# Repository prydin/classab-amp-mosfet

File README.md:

# 50W Class AB MOSFET Amplififier

## Disclaimer
This amplifier has been built and tested and, at least subjectively speaking, sounds great. However, I'm not a professional designer
and this is my first "serious" attempt at amplifier design. I invite you to build this amplifier if you like, but don't expect it to
perform like a professionally designed high-end amplifier. That said, I think it sounds pretty darn good. 

## Background
This is an updated version of the bipolar Class AB amplifier I designed a while ago that can be found here: https://github.com/prydin/classab-amp
I tried to correct some of the mistakes (mostly in the PCB design) and I also wanted to try use MOSFETs for the output stage. I settled on the 
tried and tested IRFP240/9240 combination. Although not marketed as audio transistors, these devices have found their way into countless amplifier 
designs, perhaps most notably some of Nelson Pass' First Watt creations. I really like the way they're performing. They seem to run a lot cooler
at the same quiescent current compared to their BJT counterparts. I'm also seeing less distortion and mostly concentrated on the second harmonic.

## Repository structure
* `kicad` - Schematic and PCB layout in KiCAD format
*  `spice` - LTSpice simulations

## Overall design
The design is a simple single differential stage amplifier with a single ended, two transistor emitter coupled VAS driving two complementary
MOSFETs on the output.

### Input stage
After the customary DC-blocking capacitor and RF filter, the signal is fed into a long tailed pair differential amplifier that's enhanced to 
an active current sink and current mirror loads. The active sink and load helps improve both distortion and frequency response. The bias 
current of the LTP is set to approximately 1.5mA. The LTP and its current mirrors are placed closely togethe for maximum heat
condudctivity between the transistors. If so desired, they can be put into physical contact using a brace or a zip tied.
The feedback is fed through a 22k/1k voltage divider, yielding about 23x (27dB) gain. This is a conservative estimate and may have to 
be adjusted when testing the physical build. The active current sink and load seem to offer a robustpower supply rejection. 

### Voltage amplification/drive stage
I went for a very simple single-sided design here. I've gotten many suggestions that I should try a dual differential design instead, but 
the current design seems good enough, so I stuck with it. The VAS has a 220pF compensation capacitor which appears to be enough to provide 
ample phase margin. 

### Output stage biasing
The output stage is biased using a servo transistor driven by a constant current sink. The BD139 for the servo as chosen just because it's
easy to mount on a heat sink together with the power components for good heat conductivity between components. A much less powerful 
transistor works too, but would have been harder to attach to the heat sink.

### Output stage
The output stage consists of a complementary pair made up of IRFP240/9240 MOSFETs with a 330ohm gate resistor. 
Before the signal reaches the speaker, it is passed througha snubber and an inductor to further improve stability.

### Short circuit projection 
Rather than the "base current thief" arrangement in the BJT version, I'm solely relying on a pair of zener diodes to keep the 
gate voltage about 5V above or below the source voltage. This limits the power to about 50W and results in fairly soft clipping. 

### Output coil
The output coil is realized simply by winding 10-12 turns of 16 AWG wire around R21. See the photo below!

### Power improvements
Altough this hasn't been tested or thorouhgly analyzed, it should be possible to increase the rail voltages to +-40V, which yields about
160W according to simultions. For this to work, the gain needs to be made higher by increasing the value of the feedback resistor. The voltage 
limiting zener diodes on the gates also have to be adjusted.

### Power supply
The amplifier is intended to be powered by an unregulated linear power supply like the one supplied in this repository. Each amplifier board
is fitted with 4700uF on each rail, per channel and the rectifier board has an additional 9400uF on each rail. In simulations, measurements 
and listening tests, this seems sufficient. 

The amplifier has been tested with rail voltages ranging from +-24V to +-37V with good results. Obviously, higher output power requires more voltage. 
The recommended supply voltage range is +-24V to +-40V. 

In my build, I'm using a 2x25V toroidial transformer. Where I live, this ended up giving me 2x39V rectified voltage, which is a bit overkill for
50W, but some extra headroom is never a bad thing.

### PCB Design
I am *NOT* an expert at PCB design. In fact, I'm very much a novice and not very good at it, so the PCB layout is probably somewhat naive. 
In this design, I tried to create a star arrangement for the power ground. The power ground is loosely connected to the signal ground through 
a 100ohm resistor and to the chassis through a 220ohm resistor and a 10nF capacitor. This is slightly different from the prototype that I 
originally built, so you may have to tweak this if you experience hum. The prototype I'm currently using in my livingroom has no audible hum.

# Build and bring-up

## Mechanincal design
Mechnical design is not my forte, so you're probably best off to come up with your own design here. I went with a 11' x 10' metal case
from Nobsound. This proved to be rather small with the beefy 250VA transformer I picked, so wire routing turned out to be a challenge. 
I wouldn't be offended if you called it a rat's nest. I used a pair of inexpensive finned aluminum heatsinks from Amazon and they seem to 
work very well. During casual listening at a moderate volume, they stay more or less room temperature. 

## Thermal coupling
It is *extremely* important that Q7, Q9 and Q10 are thermally coupled, i.e. mounted on the same heat sink. Failure to do this 
may result in thermal runaway and catastrophic damage to the output stage! 

You may also want to thermally couple the two transistor pairs in the input stage (R1 and R2, and R3 and R4 respectively). I just 
wrapped a piece if ziptie around them to make them touch. 

## Bring-up
This is the procedure I followed when bringing it up the first time. It saved me on the first bring-up since I had accidentally mixed up 
the transistors in the LTP which put DC on the speaker output.

1. Disconnect the speakers.
2. Turn the bias trimmer to its lowest setting (highest resistance)
3. Connect a current limited power supply with -12V, 0V and +12V to the power inputs. Limit the current to 200mA. The amplifier should draw less than 100mA.
4. Measure the DC voltage across the speaker terminals. It should be less than 50mV. 
5. Connect an oscilloscope to the output. There should be no oscillations.
6. Slowly bring the voltage to +/-24V. The current draw should still be well below 100mA.
7. Connect a 8Ω resistive dummy load to the output. The current draw should not increase significantly.
8. Connect a signal generator to the input and send in a 10mV p/p 1kHz sine singal. You should see approximately 200mV p/p on the speaker output.
9. Increase the current limit to 500mA and try the same with a 100mV p/p and 200mV p/p signal.
10. Increase the current limit to 1A and try a 300mV p/p input.
11. Connect the speakers and feed a music signal. It it may not sound perfect, since lab supplies aren't designed to power amplifiers, but there should be no severe distortion. 
13. Hook up the amplifier to the power supply that will be used for the final build. I put 3A fuses in series with each rail.
14. Measure DC voltage on the speaker outputs. The DC voltage should not exceed 50mV. 
15. Measure the voltage between the emitters on the output transistors (Q9 and Q10). Adjust the bias trim until the voltage reaches 20mV. This corresponds to a bias current of 30mA.
    Verify that the heat sinks are no warmer than luke warm. You may go higher or lower depending on your preferences. Just watch the temperatures!
17. Bring up the amplifer and test it using a dummy load and signal generator as described above.
18. If all has gone well up until this point, connect your speakers and crank up your favorite tune. ENJOY!

# Schematic

## Stats

All simulations are done with an 8 ohm resistive dummy load, 1V input at 1kHz.

### THD (simulated)
At a fairly moderate quiescent current of 45mA, I get a THD20k of 0.003% at 30% power. A THD below 0.1% is considered to be inaudible, so these numbers
are fine by me. I know there are audiophiles who insist on THD numbers <0.0001%, but I'm not one of them. Inaudible is just fine by me. The THD at full
power (50W) is about 0.1%.

I unfortunately don't have the equipment to accurately measure THD in the lab, but it looks to be considerably below 0.1% (probably below 0.01%).

```
Fourier components of V(out)
DC component:-0.00638947

Harmonic	Frequency	 Fourier 	Normalized	 Phase  	Normalized
 Number 	  [Hz]   	Component	 Component	[degree]	Phase [deg]
    1   	 1.000e+3	 1.137e+1	 1.000e+0	   90.67°	    0.00°
    2   	 2.000e+3	 2.313e-4	 2.034e-5	  -82.88°	 -173.56°
    3   	 3.000e+3	 1.539e-4	 1.354e-5	  176.54°	   85.87°
    4   	 4.000e+3	 1.334e-4	 1.174e-5	  -87.58°	 -178.26°
    5   	 5.000e+3	 1.239e-5	 1.090e-6	 -166.62°	 -257.29°
    6   	 6.000e+3	 9.620e-5	 8.462e-6	  -84.00°	 -174.67°
    7   	 7.000e+3	 5.301e-5	 4.663e-6	    6.49°	  -84.19°
    8   	 8.000e+3	 6.785e-5	 5.968e-6	  -81.59°	 -172.26°
    9   	 9.000e+3	 6.897e-5	 6.067e-6	    8.04°	  -82.64°
   10   	 1.000e+4	 4.481e-5	 3.942e-6	  -78.43°	 -169.11°
   11   	 1.100e+4	 6.376e-5	 5.608e-6	    9.49°	  -81.19°
   12   	 1.200e+4	 2.633e-5	 2.316e-6	  -73.92°	 -164.59°
   13   	 1.300e+4	 5.062e-5	 4.453e-6	   10.82°	  -79.85°
   14   	 1.400e+4	 1.270e-5	 1.117e-6	  -65.17°	 -155.85°
   15   	 1.500e+4	 3.641e-5	 3.203e-6	   11.89°	  -78.79°
   16   	 1.600e+4	 4.245e-6	 3.734e-7	  -33.69°	 -124.37°
   17   	 1.700e+4	 2.420e-5	 2.129e-6	   12.70°	  -77.97°
   18   	 1.800e+4	 3.632e-6	 3.195e-7	   53.21°	  -37.47°
   19   	 1.900e+4	 1.499e-5	 1.318e-6	   12.97°	  -77.70°
   20   	 2.000e+4	 5.428e-6	 4.775e-7	   75.45°	  -15.22°
Harmonic Distortion: 0.003150%
```

### AC Analysis (measured)
The amplifier has a 3dB bandwidth of about 250kHz, which is respectable, while not in the hardcore audiophile range, but it keeps any poles far away from the audible 
range to make both the amplitude and phase response vritually flat where it matters. I am of the opinion that nothing >20kHz has any impact on
the listening experience.

# Bill of materials

All capacitor voltages are 50V and all resistor power ratings are 1/4W unless otherwise indicated. 
1% tolerance resistors are recommended.

## Amplifier Board (each channel)

| Reference | Value | Footprint | Qty | Vendor| Part No | 
| --------- | ----- | --------- | ----| ----- | ------- |
| C1 | 33uF, non-polarized | Radial_D4.0mm_P2.00mm | 1 | Generic | | 
| C2,C5 | 100pF | Rect_L7.2mm_W3.0mm_P5.00mm | 2 | Generic | |
| C4 | 220uF | Radial_D8.0mm_P5.00mm | 1 | Mouser | 871-B32529C1104J |
| C6 | 10uF | CRadial_D4.0mm_P2.00mm | 1 | Mouser | 710-860240672002 |
| C7 | 10nF | Rect_L7.2mm_W3.0mm_P5.00mm | 1 | Generic | |
| C13,C14 | 4700uF | CP_Radial_D18.0mm_P7.50mm | 2 | Mouser | 232-50PK4700MEFC18X4 | 
| D4,D5 | 1N4148 | DO-35_SOD27_P7.62mm | 2 | Mouser | 512-1N4148 |
| D6,D11 | 1N5919 |DO-41_SOD81_P10.16mm | 2 | Mouser | 863-1N5919BRLG |
| D7,D8,D9,D10 | 1N4004 | DO-41_SOD81_P10.16mm | 4 | Mouser | 637-1N4004 | 
| J1 | Terminal Block | TerminalBlock_Phoenix_MKDS-1,5-2_1x02_P5.00mm | 1 | Generic |
| J2,J4,J5 | Spade connector, male | Pitch 5.08mm, hole 1.4mm | 3 | Generic | |
| J3 | Terminal Block | TerminalBlock_4Ucon_1x02_P3.50mm_Horizontal | 1 | Generic | |
| Q1,Q2,Q11,Q12,Q15 | 2N5551 | TO-92_Wide | 5 | Mouser | 583-2N5551-T |
| Q3,Q4,Q16 | 2N5401 | TO-92_Wide | 3 | Mouser | 583-2N5401-F |
| Q6 | BD140 | TO-126-3_Vertical | 1 | Mouser | 511-BD140-16 |
| Q7,Q8 | BD139 | TO-126-3_Vertical | 2 | Mouser | 511-BD139-16 |
| Q9 | IRFP240 | TO-247-3_Vertical | 1 | Mouser | 844-IRFP240PBF |
| Q10 | IRFP9240 | TO-247-3_Vertical | 1 | Mouser | 844-IRFP9240PBF |
| R1 | 150 | L6.3mm_D2.5mm_P2.54mm | 1 | Mouser | 660-MF1/4LCT52R151J |
| R2,R9 | 22k | L6.3mm_D2.5mm_P2.54mm | 2 | Mouser | MFR-25FTE52-22K | 
| R3,R4,R5 | 470 | L3.6mm_D1.6mm_P7.62mm | 3 | Mouser | 660-MF1/4DCT52R4700F |
| R6,R11 | 4.7k | L3.6mm_D1.6mm_P7.62mm | 2 | Mouser | 660-MF1/4LCT52R472G |
| R7,R19 | 1k | L3.6mm_D1.6mm_P7.62mm | 2 | Mouser | 279-LR0204F1K0 |
| R8,R12,R18 | 330 | L3.6mm_D1.6mm_P7.62mm | 3 | Mouser | 660-MF1/4LCT52R331J |
| R10,R14,R22 | 100 | L3.6mm_D1.6mm_P7.62mm | 3 | Generic | |
| R13 | 10k | L3.6mm_D1.6mm_P7.62mm | 1 | Generic | |
| R15 | 220 / 3W | L11.9mm_D4.5mm_P15.24mm | 1 | Mouser | 	603-FMP300JTF73-220R |
| R16,R17 | 0.33 / 3W | L11.9mm_D4.5mm_P15.24mm | 2 | Mouser | 71-PAC300003307FAC00 |
| R20,R21 | 10 / 3W | L11.9mm_D4.5mm_P15.24mm | 2 | Mouser | EP3WSS10RJ | 
| RV1,RV2 | 300 | TRIM_T93YA103KT20 | 2 | Amazon | https://www.amazon.com/BOJACK-Multiturn-Trimmer-Potentiometer-Assortment/dp/B07WDCVGJV |

## Rectifier board

| Reference | Value | Footprint | Qty | Vendor| Part No | 
| --------- | ----- | --------- | ----| ----- | ------- |
| C1,C2,C5,C6 | 4700uF | CP_Radial_D18.0mm_P7.50mm | 4 | Mouser | 232-50PK4700MEFC18X4 | 
| C3,C4,C7 | 100n | Rect_L7.2mm_W5.5mm_P5.00mm | 3 | Generic | |
| D1,D2,D3,D4 | GI754 | D_P600_R-6_P12.70mm | 4 | Mouser | 625-GI754-E3/73 |
| J1, J2, J3, J4, J5, J6 | Spade connector, male | Pitch 5.08mm, hole 1.4mm | 6 | Generic | |

## Transformer
| Reference | Value | Footprint | Qty | Vendor| Part No | 
| --------- | ----- | --------- | ----| ----- | ------- |
| TR1 | 25V / 250VA | N/A | 1 | Avel Lindberg | Y236652 |

## Case and hardware 
* Case: https://www.aliexpress.us/item/3256807449187155.html?src=google&gatewayAdapt=glo2usa
* Heatsink: https://www.amazon.com/Awxlumv-Aluminum-60x150x25mm-2-36x5-91x0-98-Amplifier/dp/B07VDHQDQT

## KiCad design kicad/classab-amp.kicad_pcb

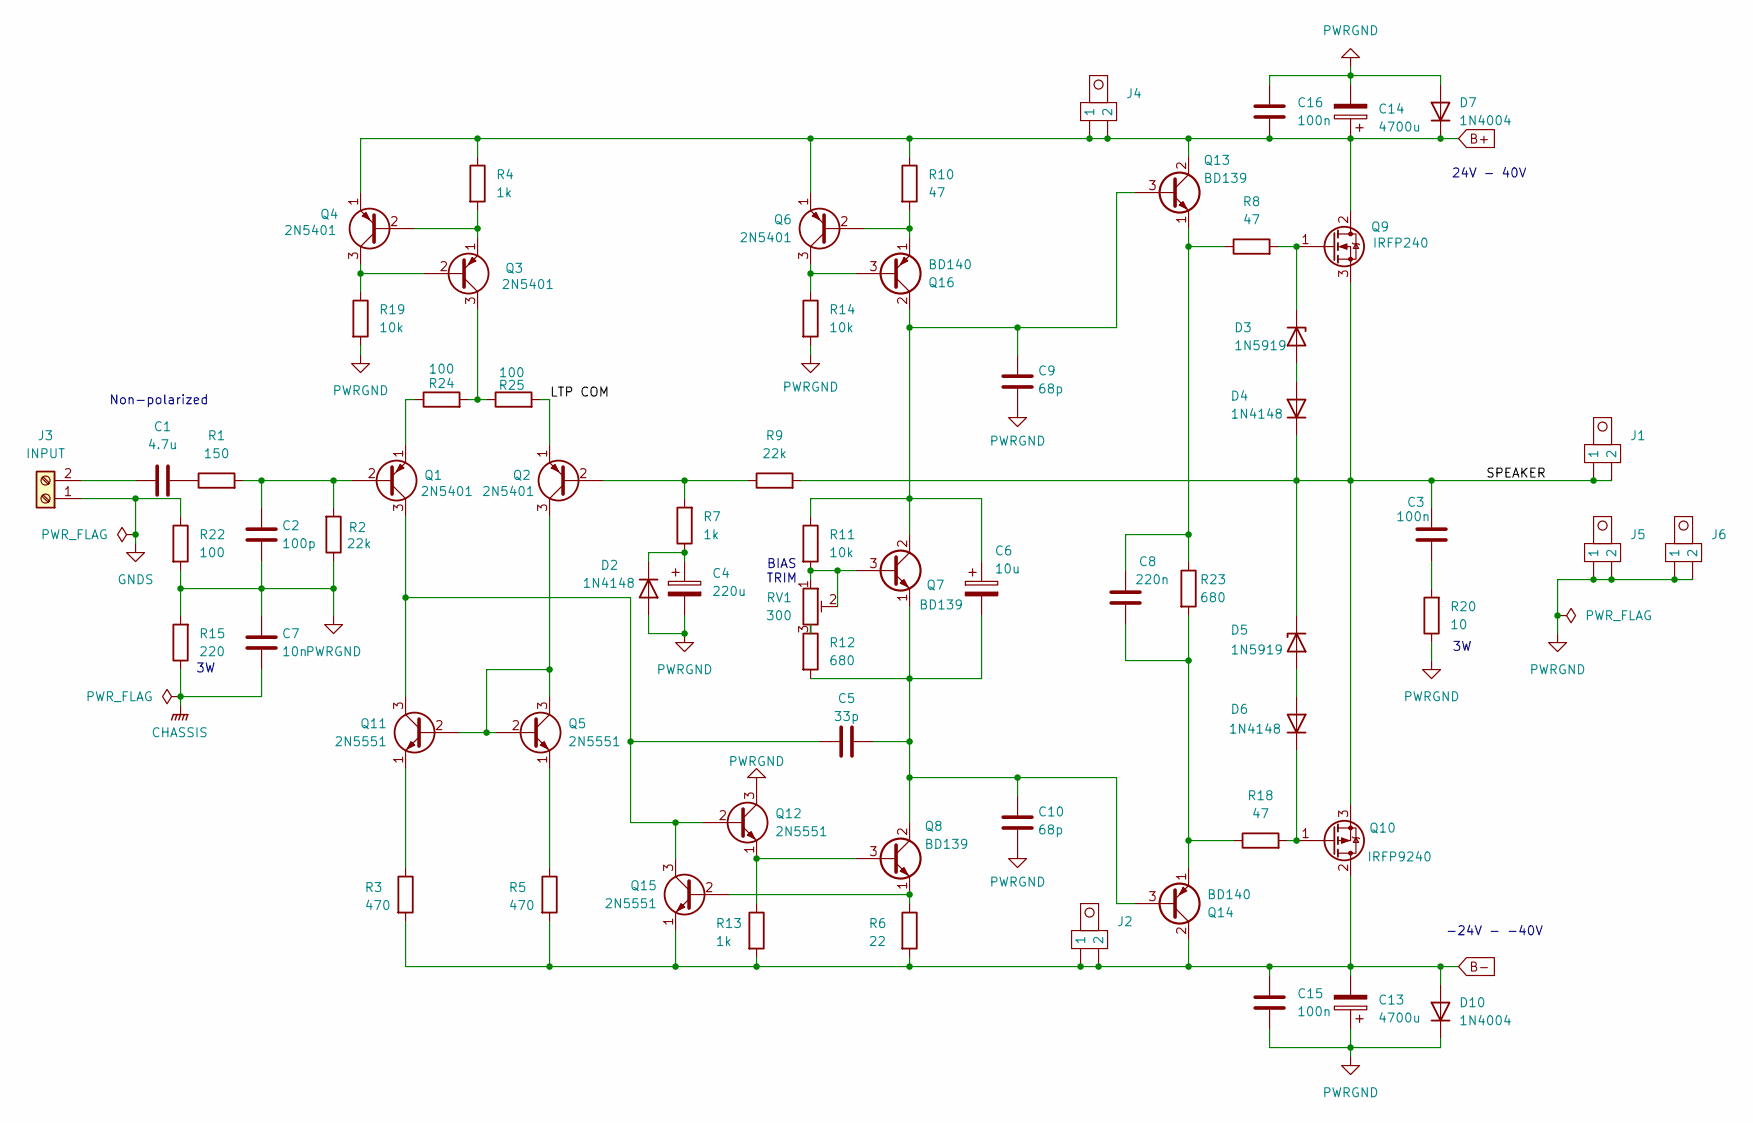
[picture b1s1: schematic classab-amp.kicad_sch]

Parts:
C1: 4.7u; CP_Radial_D4.0mm_P2.00mm
C2: 100p; C_Rect_L7.2mm_W3.0mm_P5.00mm_FKS2_FKP2_MKS2_MKP2
C3, C15, C16: 100n; C_Rect_L7.2mm_W3.0mm_P5.00mm_FKS2_FKP2_MKS2_MKP2
C4: 220u; CP_Radial_D8.0mm_P5.00mm
C5: 33p; C_Rect_L7.2mm_W3.0mm_P5.00mm_FKS2_FKP2_MKS2_MKP2
C6: 10u; CP_Radial_D4.0mm_P2.00mm
C7: 10n; C_Rect_L7.2mm_W3.0mm_P5.00mm_FKS2_FKP2_MKS2_MKP2
C8: 220n; C_Rect_L7.2mm_W3.0mm_P5.00mm_FKS2_FKP2_MKS2_MKP2
C9, C10: 68p; C_Rect_L7.2mm_W3.0mm_P5.00mm_FKS2_FKP2_MKS2_MKP2
C13, C14: 4700u; CP_Radial_D18.0mm_P7.50mm
D2, D4, D6: 1N4148; D_DO-35_SOD27_P7.62mm_Horizontal
D3, D5: 1N5919; D_DO-41_SOD81_P10.16mm_Horizontal
D7, D10: 1N4004; D_DO-41_SOD81_P10.16mm_Horizontal
J1, J2, J4, J5, J6: Spade Connector
J3: INPUT; TerminalBlock_4Ucon_1x02_P3.50mm_Horizontal
Q1, Q2, Q3, Q4, Q6: 2N5401; TO-92_Wide
Q5, Q11, Q12, Q15: 2N5551; TO-92_Wide
Q7, Q8, Q13: BD139; TO-126-3_Vertical
Q9: IRFP240; TO-247-3_Vertical
Q10: IRFP9240; TO-247-3_Vertical
Q14, Q16: BD140; TO-126-3_Vertical
R1: 150; R_Axial_DIN0204_L3.6mm_D1.6mm_P7.62mm_Horizontal
R2, R9: 22k; R_Axial_DIN0204_L3.6mm_D1.6mm_P7.62mm_Horizontal
R3, R5: 470; R_Axial_DIN0204_L3.6mm_D1.6mm_P7.62mm_Horizontal
R4, R7, R13: 1k; R_Axial_DIN0204_L3.6mm_D1.6mm_P7.62mm_Horizontal
R6: 22; R_Axial_DIN0204_L3.6mm_D1.6mm_P7.62mm_Horizontal
R8, R10, R18: 47; R_Axial_DIN0204_L3.6mm_D1.6mm_P7.62mm_Horizontal
R11: 10k; R_Axial_DIN0207_L6.3mm_D2.5mm_P2.54mm_Vertical
R12: 680; R_Axial_DIN0207_L6.3mm_D2.5mm_P2.54mm_Vertical
R14, R19: 10k; R_Axial_DIN0204_L3.6mm_D1.6mm_P7.62mm_Horizontal
R15: 220; R_Axial_DIN0414_L11.9mm_D4.5mm_P15.24mm_Horizontal
R20: 10; R_Axial_DIN0414_L11.9mm_D4.5mm_P15.24mm_Horizontal
R22: 100; R_Axial_DIN0204_L3.6mm_D1.6mm_P7.62mm_Horizontal
R23: 680; R_Axial_DIN0204_L3.6mm_D1.6mm_P7.62mm_Horizontal
R24, R25: 100; R_Axial_DIN0207_L6.3mm_D2.5mm_P2.54mm_Vertical
RV1: 300; TRIM_T93YA103KT20

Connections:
/LTP COM: Q2.1 (E), R25.2; also elsewhere on the board
/SPEAKER: C3.1, D4.1 (K), D5.1 (K), J1.1, J1.2, Q9.3 (S), Q10.3 (S), R9.2
B-: C13.2, C15.1, D10.2 (A), J2.1, J2.2, Q10.2 (D), Q14.2 (C), Q15.1 (E), R3.2, R5.2, R6.2, R13.2
GNDS: J3.1, R22.1
unnamed: C1.2, R1.1
unnamed: C3.2, R20.2
unnamed 6: Q2.2 (B), R7.2, R9.1; also elsewhere on the board
unnamed: C4.1, D2.1 (K), R7.1
unnamed: D3.2 (A), D4.2 (A)
unnamed: D3.1 (K), Q9.1 (G), R8.2
unnamed: D5.2 (A), D6.2 (A)
unnamed: D6.1 (K), Q10.1 (G), R18.2
unnamed 12: C2.1, Q1.2 (B), R1.2, R2.2; also elsewhere on the board
unnamed: C1.1, J3.2
unnamed: C5.1, Q1.3 (C), Q11.3 (C), Q12.2 (B), Q15.3 (C)
unnamed: Q1.1 (E), R24.1
unnamed: Q3.2 (B), Q4.3 (C), R19.1
unnamed: Q3.3 (C), R24.2, R25.1
unnamed: Q3.1 (E), Q4.2 (B), R4.2
unnamed: Q5.1 (E), R5.1
unnamed: Q7.3 (B), R11.2, RV1.1, RV1.2
unnamed: Q2.3 (C), Q5.2 (B), Q5.3 (C), Q11.2 (B)
unnamed: Q11.1 (E), R3.1
unnamed: Q8.3 (B), Q12.1 (E), R13.1
unnamed: C6.1, C9.1, Q7.2 (C), Q13.3 (B), Q16.2 (C), R11.1
unnamed: C8.1, Q13.1 (E), R8.1, R23.1
unnamed: C5.2, C6.2, C10.1, Q7.1 (E), Q8.2 (C), Q14.3 (B), R12.2
unnamed: C8.2, Q14.1 (E), R18.1, R23.2
unnamed: Q8.1 (E), Q15.2 (B), R6.1
unnamed: Q6.3 (C), Q16.3 (B), R14.1
unnamed: Q6.2 (B), Q16.1 (E), R10.2
unnamed: R12.1, RV1.3

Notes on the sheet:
BIAS TRIM
-24V - -40V
24V - 40V
Non-polarized

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
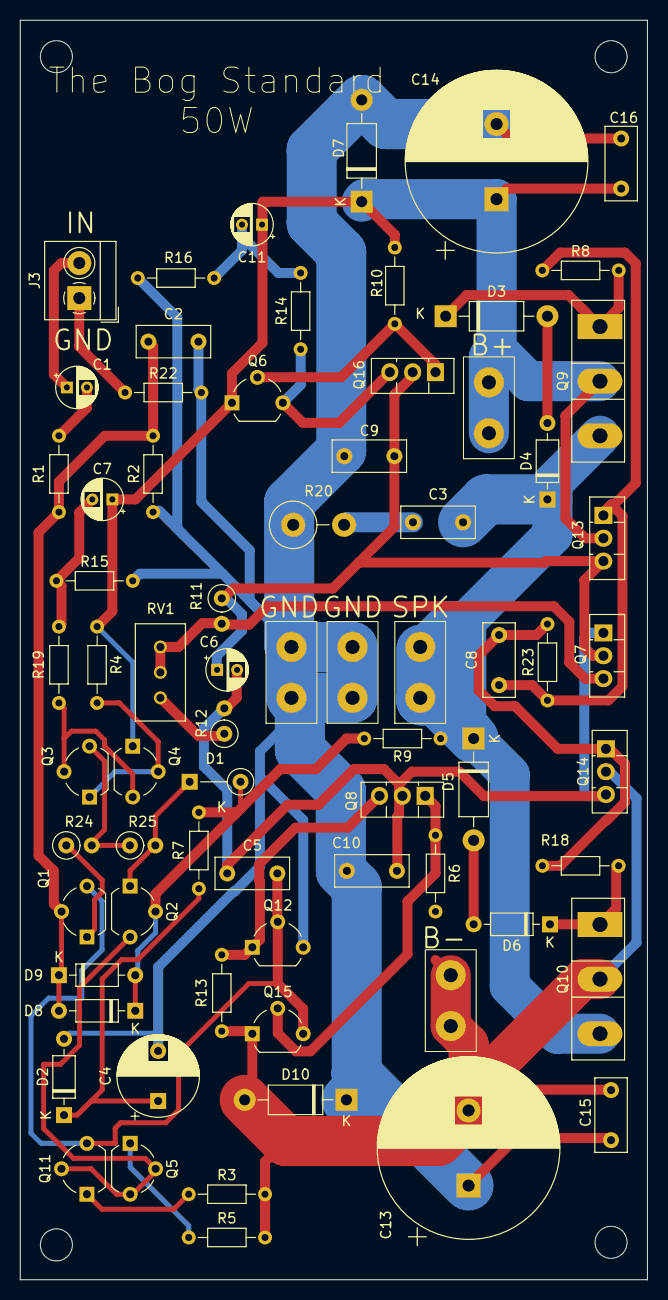
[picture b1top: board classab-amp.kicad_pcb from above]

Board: 2 copper layers, 62.6 x 125.7 mm, 71 parts (0 on the bottom side), 36 nets.

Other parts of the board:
C11: 4.7u; CP_Radial_D4.0mm_P2.00mm
D1: 1N4148; D_DO-35_SOD27_P5.08mm_Vertical_KathodeUp
D8, D9: 1N4148; D_DO-35_SOD27_P7.62mm_Horizontal
R16: 4.7k; R_Axial_DIN0204_L3.6mm_D1.6mm_P7.62mm_Horizontal

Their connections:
/LTP COM: D1.1 (K); also elsewhere on the board
unnamed 6: D1.2 (A), D8.1 (K), D9.2 (A); also elsewhere on the board
unnamed 12: D8.2 (A), D9.1 (K); also elsewhere on the board

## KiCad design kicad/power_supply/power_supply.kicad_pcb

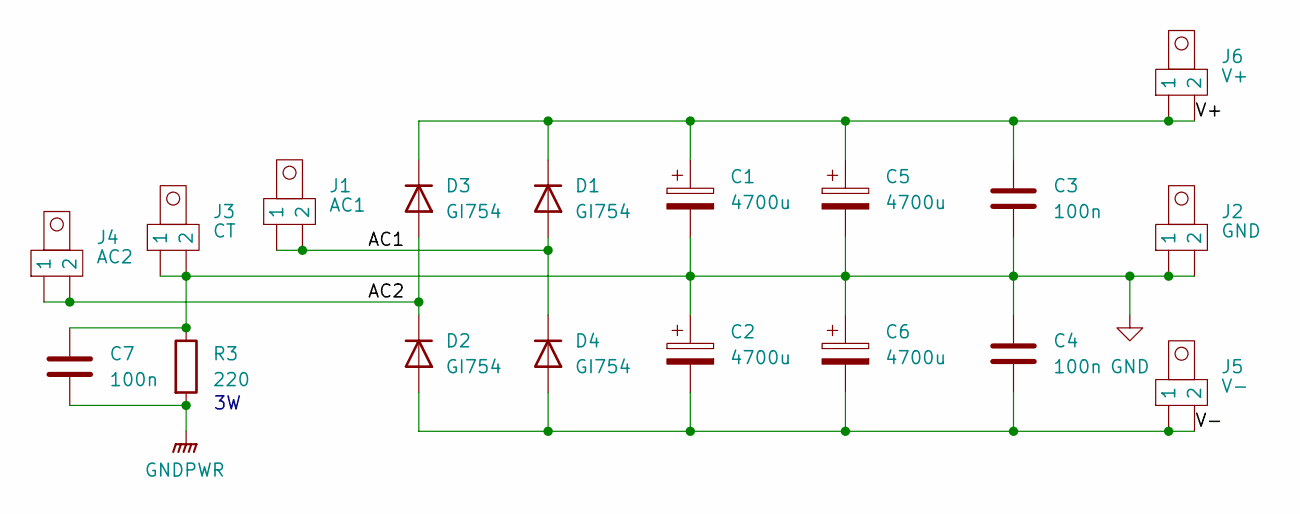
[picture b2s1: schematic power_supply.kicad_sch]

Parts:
C1, C2, C5, C6: 4700u; CP_Radial_D18.0mm_P7.50mm
C3, C4, C7: 100n; C_Rect_L7.2mm_W5.5mm_P5.00mm_FKS2_FKP2_MKS2_MKP2
D1, D2, D3, D4: GI754; D_P600_R-6_P12.70mm_Horizontal
J1: AC1; Spade Connector
J2: GND; Spade Connector
J3: CT; Spade Connector
J4: AC2; Spade Connector
J5: V-; Spade Connector
J6: V+; Spade Connector
R3: 220; R_Axial_DIN0414_L11.9mm_D4.5mm_P7.62mm_Vertical

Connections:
/AC1: D1.2 (A), D4.1 (K), J1.1, J1.2
/AC2: D2.1 (K), D3.2 (A), J4.1, J4.2
/V+: C1.1, C3.1, C5.1, D1.1 (K), D3.1 (K), J6.1, J6.2; also elsewhere on the board
/V-: C2.2, C4.2, C6.2, D2.2 (A), D4.2 (A), J5.1, J5.2; also elsewhere on the board
GND: C1.2, C2.1, C3.2, C4.1, C5.2, C6.1, C7.1, J2.1, J2.2, J3.1, J3.2, R3.1; also elsewhere on the board
GNDPWR: C7.2, R3.2

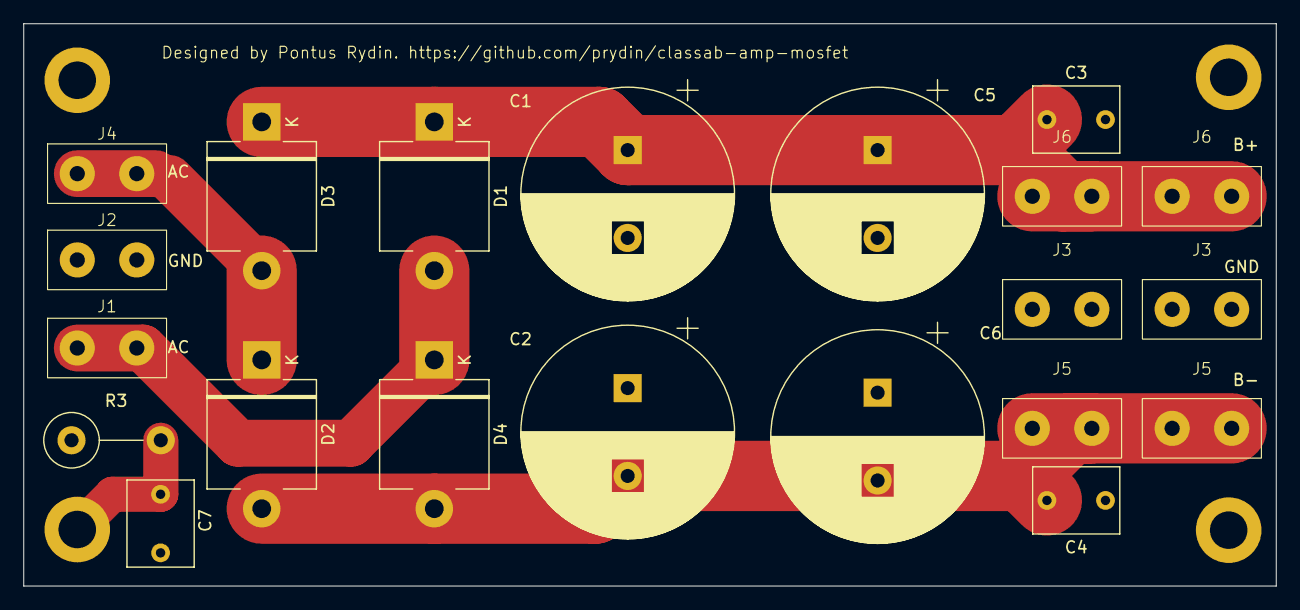
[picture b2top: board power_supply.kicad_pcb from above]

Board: 2 copper layers, 106.9 x 48.0 mm, 21 parts (0 on the bottom side), 6 nets.

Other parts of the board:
J3#2: CT; Spade Connector
J5#2: V-; Spade Connector
J6#2: V+; Spade Connector

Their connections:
/V+: J6#2.1, J6#2.2; also elsewhere on the board
/V-: J5#2.1, J5#2.2; also elsewhere on the board
GND: J3#2.1, J3#2.2; also elsewhere on the board

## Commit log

2024-10-25 Production candidate
2024-11-21 Public release candidate
2024-11-22 Updated images
2024-11-22 Added chassis image
2024-11-22 Adjusted power supply
2024-11-23 Minor changes
2025-01-25 Added protection diode for VAS. Removed offset pot.
2025-01-26 2.0 stuff
2025-01-30 Pre re-layout
